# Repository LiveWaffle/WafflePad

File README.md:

# WafflePad

| Bill Of Materials  | Quanity |
| ------------- | ------------- |
| SW_Cherry_MX_1.00u_PCB | 6 |
| ??? | 3 |
| D_DO-35_SOD27_P7.62mm_Horizontal | 6 |
| XIAO-Generic-Thruhole-14P-2.54-21X17.8MM  | 1 |
| Bourns-PEC11R-4220F-S0024-0-0-0  | 1 |
| M2.5 X 13mm Long, Phillips Pan Head, Stainless Steel Machine Screw | 4 |
|M2.0 Hex Nuts| 4 |

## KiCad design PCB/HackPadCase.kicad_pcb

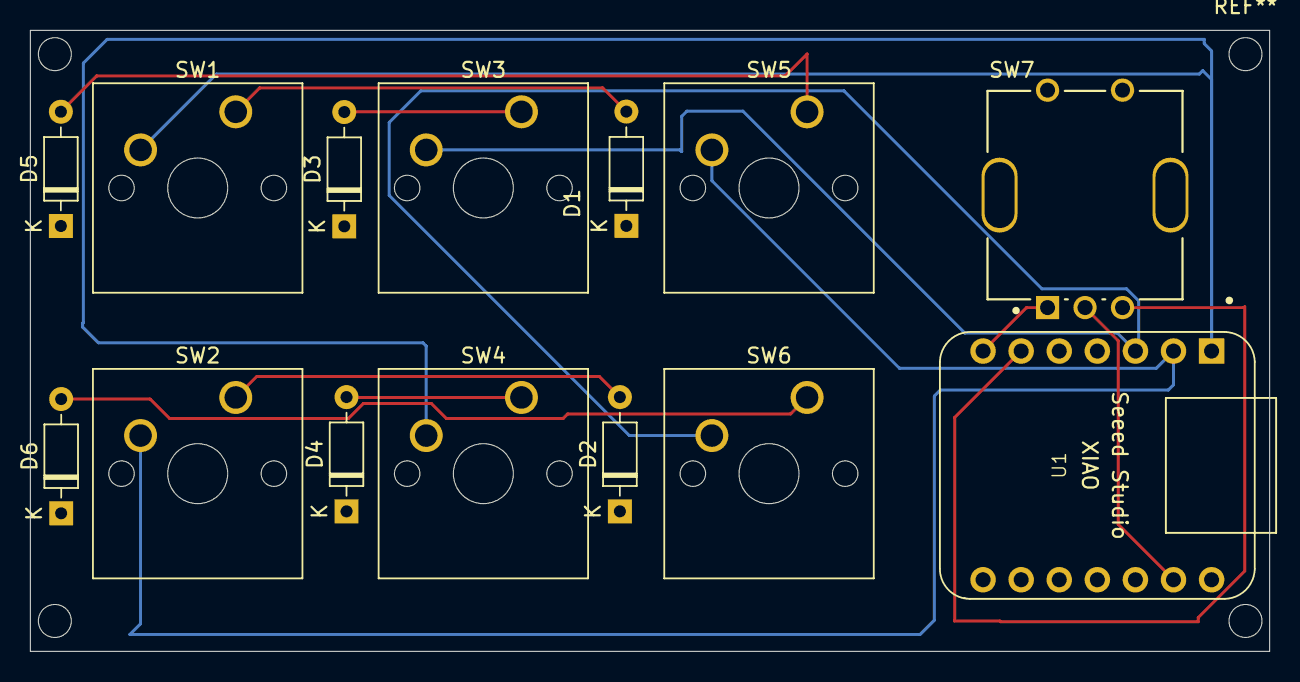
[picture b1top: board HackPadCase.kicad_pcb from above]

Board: 2 copper layers, 82.6 x 41.4 mm, 14 parts (0 on the bottom side), 14 nets.

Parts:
D1, D2, D3, D4, D5, D6: 1N4148; D_DO-35_SOD27_P7.62mm_Horizontal
SW1, SW2, SW3, SW4, SW5, SW6: SW_Push; SW_Cherry_MX_1.00u_PCB
SW7: RotaryEncoder_Switch; Bourns-PEC11R-4220F-S0024-0-0-0
U1: Seeed Studio XIAO SAMD21; XIAO-Generic-Thruhole-14P-2.54-21X17.8MM

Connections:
Column 1: SW1.2, SW4.2, U1.1 (PA02_A0_D0)
Column 2: SW2.2, SW5.2, U1.2 (PA4_A1_D1)
Column 3: SW3.2, SW6.2, U1.3 (PA10_A2_D2)
unnamed: D1.2 (A), SW1.1
unnamed: D2.2 (A), SW2.1
unnamed: D3.2 (A), SW3.1
unnamed: D4.2 (A), SW4.1
unnamed: D5.2 (A), SW5.1
unnamed: D6.2 (A), SW6.1
unnamed: SW7.C, U1.13 (GND)
unnamed: SW7.B, U1.6 (PA9_A5_D5_SCL)
unnamed: SW7.A, U1.7 (PB08_A6_D6_TX)
Row 1: D1.1 (K), D2.1 (K), D3.1 (K), U1.4 (PA11_A3_D3)
Row 2: D4.1 (K), D5.1 (K), D6.1 (K), U1.5 (PA8_A4_D4_SDA)

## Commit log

2024-10-04 Add Files for tmr
2024-10-04 upd8
2024-10-21 Organization + Fix
2024-10-21 Update PCB
2024-10-22 update changes
